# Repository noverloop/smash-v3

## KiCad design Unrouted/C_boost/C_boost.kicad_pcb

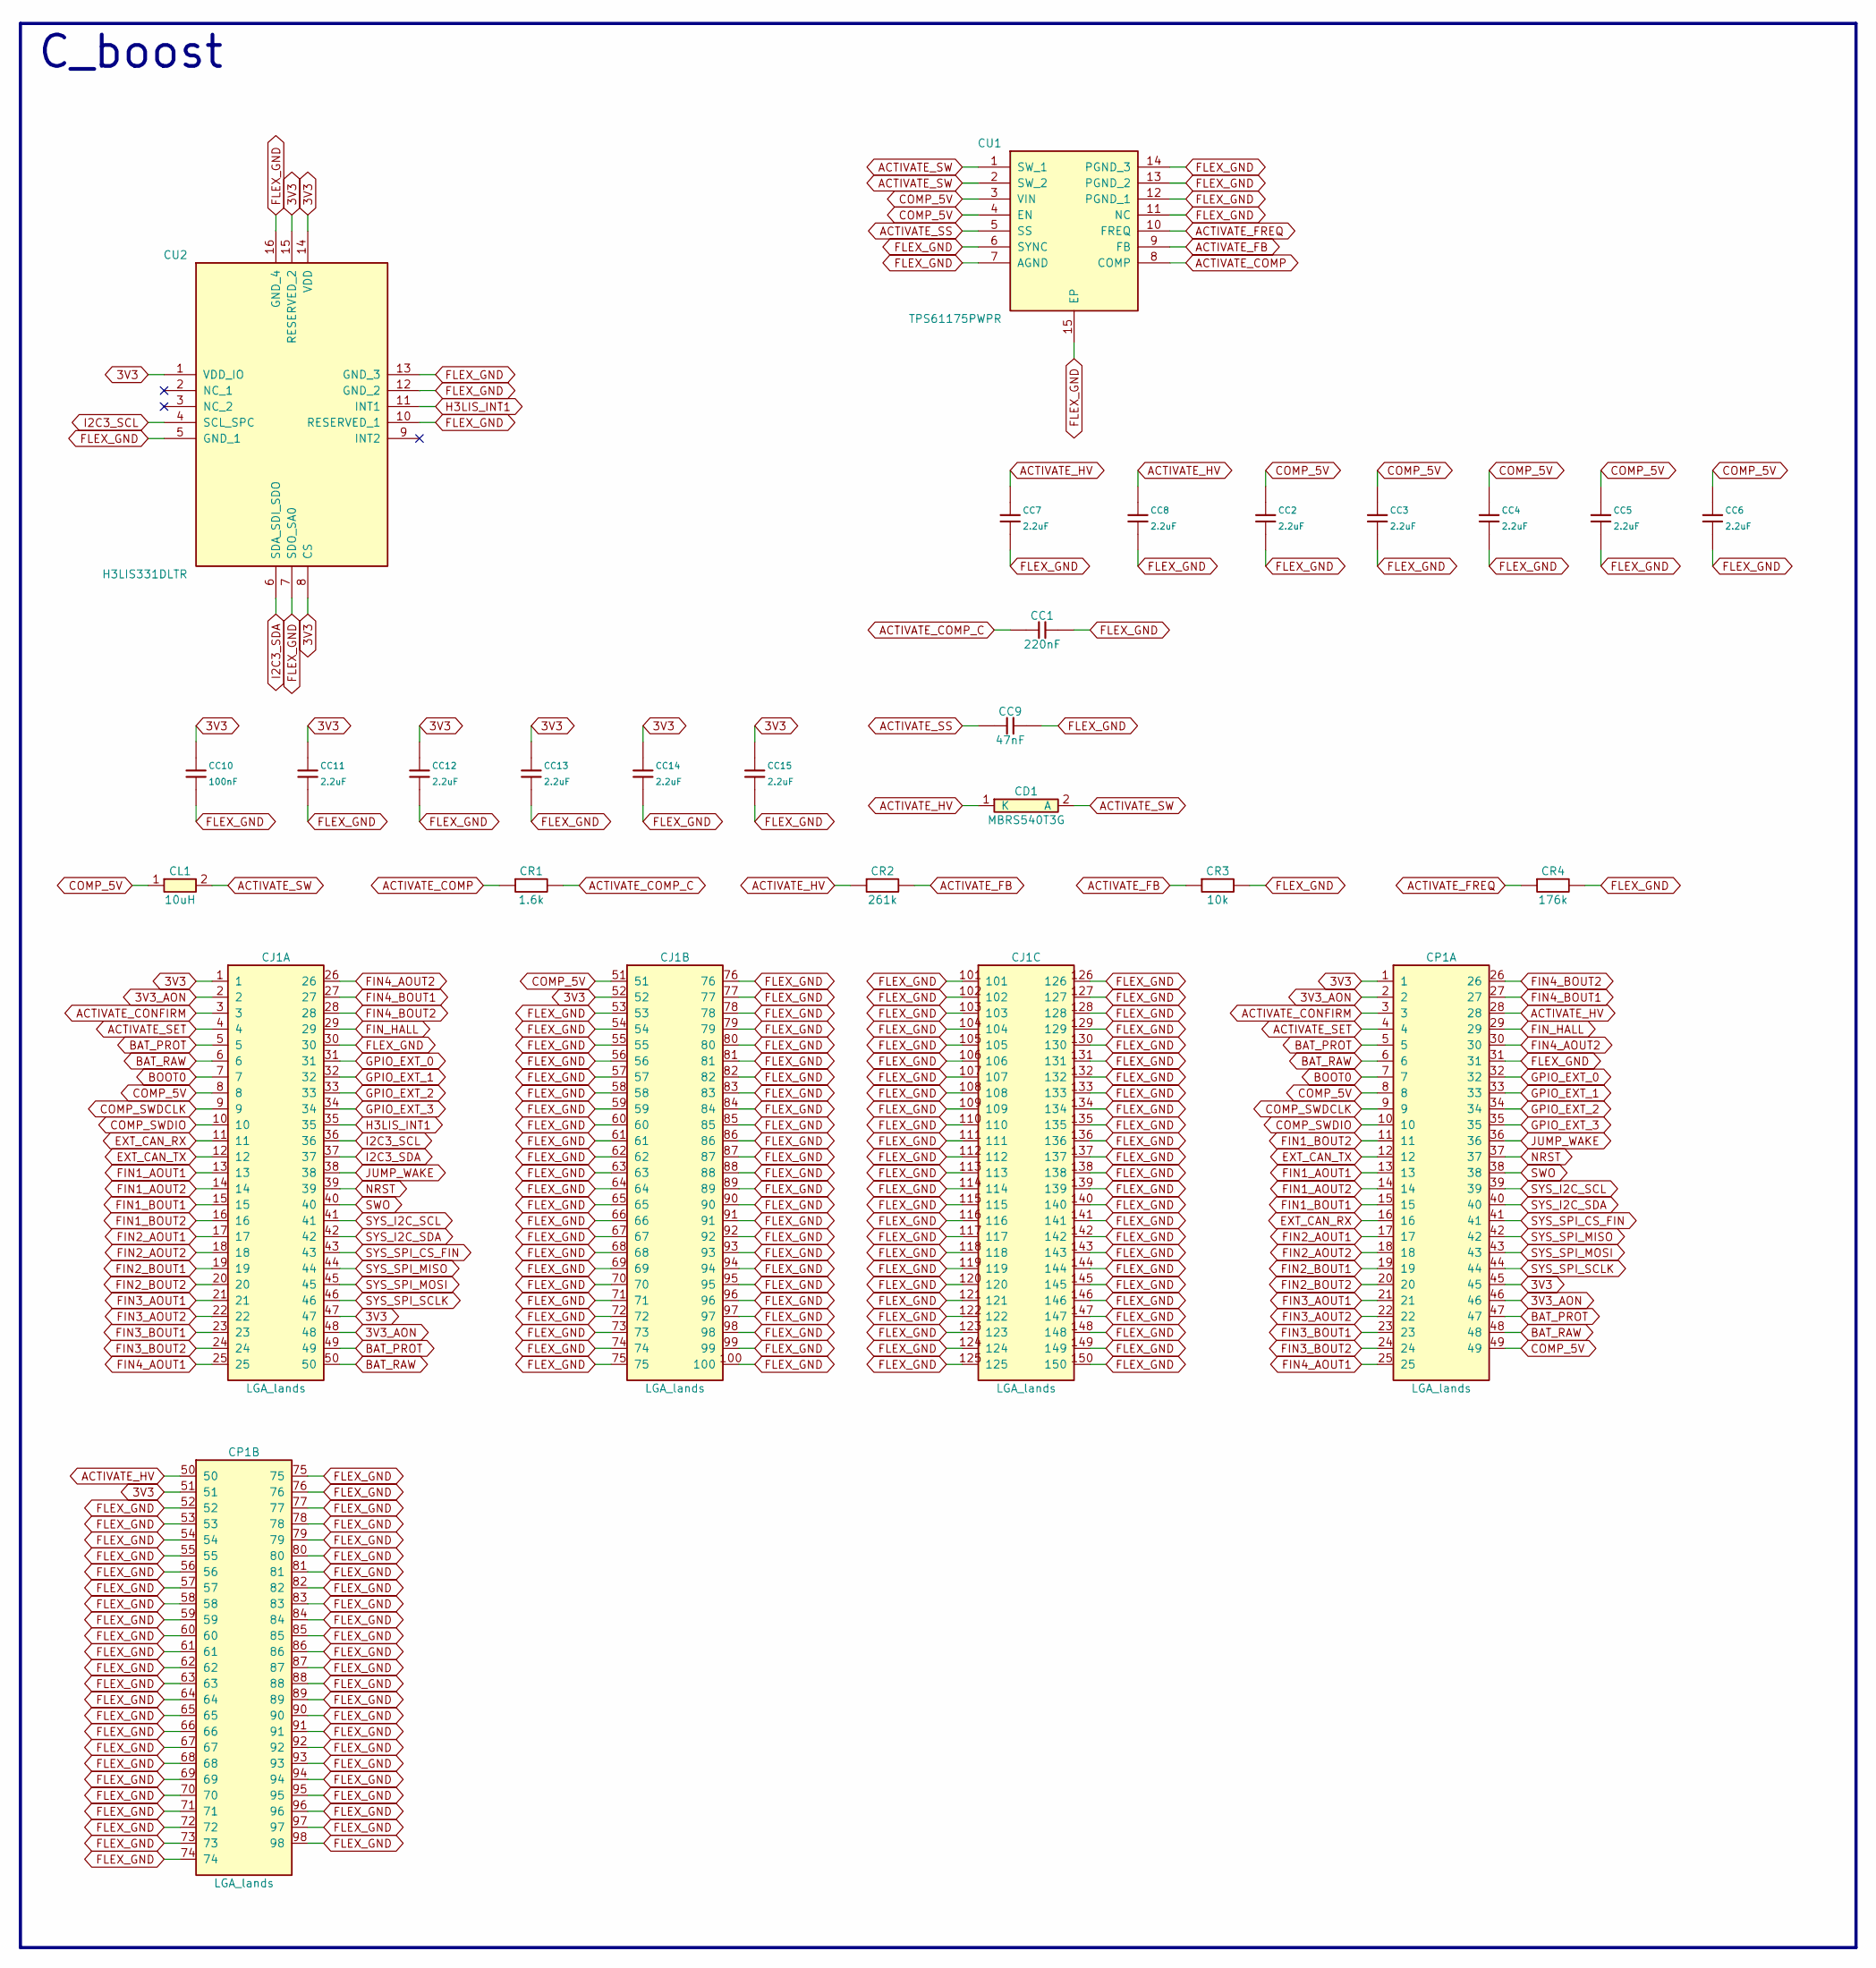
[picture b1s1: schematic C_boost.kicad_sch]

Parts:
CC1: 220nF; Capacitor_SMD_C_0603_1608Metric; MPN C-Series MIL-PRF-32535 X7R 0603 220nF
CC2, CC3, CC4, CC5, CC6, CC7, CC8, CC11, CC12, CC13, CC14, CC15: 2.2uF; Capacitor_SMD_C_0603_1608Metric; MPN C-Series MIL-PRF-32535 X7R 0603 2.2uF
CC9: 47nF; Capacitor_SMD_C_0402_1005Metric; MPN C0402 X7R 47nF
CC10: 100nF; Capacitor_SMD_C_0402_1005Metric; MPN C0402 X7R 100nF
CD1: MBRS540T3G; DIOM7958X256N; MPN MBRS540T3G
CJ1: LGA_lands; J_activation_interface_spacer_activation_interface_cell_flo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; MPN LGA_lands
CL1: 10uH; INDPM4848X280N; MPN 744043100
CP1: LGA_lands; P_activation_interface_spacer_aft_end_board_activation_inte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; MPN LGA_lands
CR1: 1.6k; Resistor_SMD_R_0402_1005Metric; MPN CRCW0402 1.6k 1% e3
CR2: 261k; Resistor_SMD_R_0402_1005Metric; MPN CRCW0402 261k 1% e3
CR3: 10k; Resistor_SMD_R_0402_1005Metric; MPN CRCW0402 10k 1% e3
CR4: 176k; Resistor_SMD_R_0402_1005Metric; MPN CRCW0402 176k 1% e3
CU1: TPS61175PWPR; SOP65P640X120-15N; MPN TPS61175PWPR
CU2: H3LIS331DLTR; LIS3DHTR (LGA-16); MPN H3LIS331DLTR

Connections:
3V3: CC10.1, CC11.1, CC12.1, CC13.1, CC14.1, CC15.1, CJ1.1, CJ1.47, CJ1.52, CP1.1, CP1.45, CP1.51, CU2.1 (VDD_IO), CU2.8 (CS), CU2.14 (VDD), CU2.15 (RESERVED_2)
3V3_AON: CJ1.2, CJ1.48, CP1.2, CP1.46
ACTIVATE_COMP: CR1.1, CU1.8 (COMP)
ACTIVATE_COMP_C: CC1.1, CR1.2
ACTIVATE_CONFIRM: CJ1.3, CP1.3
ACTIVATE_FB: CR2.2, CR3.1, CU1.9 (FB)
ACTIVATE_FREQ: CR4.1, CU1.10 (FREQ)
ACTIVATE_HV: CC7.1, CC8.1, CD1.1 (K), CP1.28, CP1.50, CR2.1
ACTIVATE_SET: CJ1.4, CP1.4
ACTIVATE_SS: CC9.1, CU1.5 (SS)
ACTIVATE_SW: CD1.2 (A), CL1.2, CU1.1 (SW_1), CU1.2 (SW_2)
BAT_PROT: CJ1.5, CJ1.49, CP1.5, CP1.47
BAT_RAW: CJ1.6, CJ1.50, CP1.6, CP1.48
BOOT0: CJ1.7, CP1.7
COMP_5V: CC2.1, CC3.1, CC4.1, CC5.1, CC6.1, CJ1.8, CJ1.51, CL1.1, CP1.8, CP1.49, CU1.3 (VIN), CU1.4 (EN)
COMP_SWDCLK: CJ1.9, CP1.9
COMP_SWDIO: CJ1.10, CP1.10
EXT_CAN_RX: CJ1.11, CP1.16
EXT_CAN_TX: CJ1.12, CP1.12
FIN1_AOUT1: CJ1.13, CP1.13
FIN1_AOUT2: CJ1.14, CP1.14
FIN1_BOUT1: CJ1.15, CP1.15
FIN1_BOUT2: CJ1.16, CP1.11
FIN2_AOUT1: CJ1.17, CP1.17
FIN2_AOUT2: CJ1.18, CP1.18
FIN2_BOUT1: CJ1.19, CP1.19
FIN2_BOUT2: CJ1.20, CP1.20
FIN3_AOUT1: CJ1.21, CP1.21
FIN3_AOUT2: CJ1.22, CP1.22
FIN3_BOUT1: CJ1.23, CP1.23
FIN3_BOUT2: CJ1.24, CP1.24
FIN4_AOUT1: CJ1.25, CP1.25
FIN4_AOUT2: CJ1.26, CP1.30
FIN4_BOUT1: CJ1.27, CP1.27
FIN4_BOUT2: CJ1.28, CP1.26
FIN_HALL: CJ1.29, CP1.29
FLEX_GND: CC1.2, CC2.2, CC3.2, CC4.2, CC5.2, CC6.2, CC7.2, CC8.2, CC9.2, CC10.2, CC11.2, CC12.2, CC13.2, CC14.2, CC15.2, CJ1.30, CJ1.53, CJ1.54, CJ1.55, CJ1.56, CJ1.57, CJ1.58, CJ1.59, CJ1.60, CJ1.61, CJ1.62, CJ1.63, CJ1.64, CJ1.65, CJ1.66, CJ1.67, CJ1.68, CJ1.69, CJ1.70, CJ1.71, CJ1.72, CJ1.73, CJ1.74, CJ1.75, CJ1.76, CJ1.77, CJ1.78, CJ1.79, CJ1.80, CJ1.81, CJ1.82, CJ1.83, CJ1.84, CJ1.85, CJ1.86, CJ1.87, CJ1.88, CJ1.89, CJ1.90, CJ1.91, CJ1.92, CJ1.93, CJ1.94, CJ1.95, CJ1.96, CJ1.97, CJ1.98, CJ1.99, CJ1.100, CJ1.101, CJ1.102, CJ1.103, CJ1.104, CJ1.105, CJ1.106, CJ1.107, CJ1.108, CJ1.109, CJ1.110, CJ1.111, CJ1.112, CJ1.113, CJ1.114, CJ1.115, CJ1.116, CJ1.117, CJ1.118, CJ1.119, CJ1.120, CJ1.121, CJ1.122, CJ1.123, CJ1.124, CJ1.125, CJ1.126, CJ1.127, CJ1.128, CJ1.129, CJ1.130, CJ1.131, CJ1.132, CJ1.133, CJ1.134, CJ1.135, CJ1.136, CJ1.137, CJ1.138, CJ1.139, CJ1.140, CJ1.141, CJ1.142, CJ1.143, CJ1.144, CJ1.145, CJ1.146, CJ1.147, CJ1.148, CJ1.149, CJ1.150, CP1.31, CP1.52, CP1.53, CP1.54, CP1.55, CP1.56, CP1.57, CP1.58, CP1.59, CP1.60, CP1.61, CP1.62, CP1.63, CP1.64, CP1.65, CP1.66, CP1.67, CP1.68, CP1.69, CP1.70, CP1.71, CP1.72, CP1.73, CP1.74, CP1.75, CP1.76, CP1.77, CP1.78, CP1.79, CP1.80, CP1.81, CP1.82, CP1.83, CP1.84, CP1.85, CP1.86, CP1.87, CP1.88, CP1.89, CP1.90, CP1.91, CP1.92, CP1.93, CP1.94, CP1.95, CP1.96, CP1.97, CP1.98, CR3.2, CR4.2, CU1.6 (SYNC), CU1.7 (AGND), CU1.11 (NC), CU1.12 (PGND_1), CU1.13 (PGND_2), CU1.14 (PGND_3), CU1.15 (EP), CU2.5 (GND_1), CU2.7 (SDO_SA0), CU2.10 (RESERVED_1), CU2.12 (GND_2), CU2.13 (GND_3), CU2.16 (GND_4)
GPIO_EXT_0: CJ1.31, CP1.32
GPIO_EXT_1: CJ1.32, CP1.33
GPIO_EXT_2: CJ1.33, CP1.34
GPIO_EXT_3: CJ1.34, CP1.35
H3LIS_INT1: CJ1.35, CU2.11 (INT1)
I2C3_SCL: CJ1.36, CU2.4 (SCL_SPC)
I2C3_SDA: CJ1.37, CU2.6 (SDA_SDI_SDO)
JUMP_WAKE: CJ1.38, CP1.36
NRST: CJ1.39, CP1.37
SWO: CJ1.40, CP1.38
SYS_I2C_SCL: CJ1.41, CP1.39
SYS_I2C_SDA: CJ1.42, CP1.40
SYS_SPI_CS_FIN: CJ1.43, CP1.41
SYS_SPI_MISO: CJ1.44, CP1.42
SYS_SPI_MOSI: CJ1.45, CP1.43
SYS_SPI_SCLK: CJ1.46, CP1.44

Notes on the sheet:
C_boost

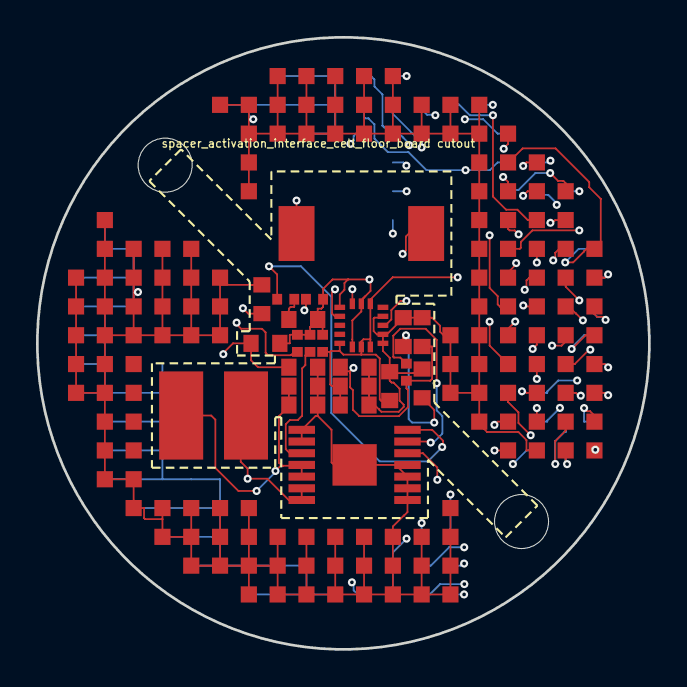
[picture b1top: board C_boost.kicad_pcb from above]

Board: 14 copper layers, 34.0 x 34.0 mm, 27 parts (1 on the bottom side), 53 nets.

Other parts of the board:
CMH1, CMH2: smash_mech_potting

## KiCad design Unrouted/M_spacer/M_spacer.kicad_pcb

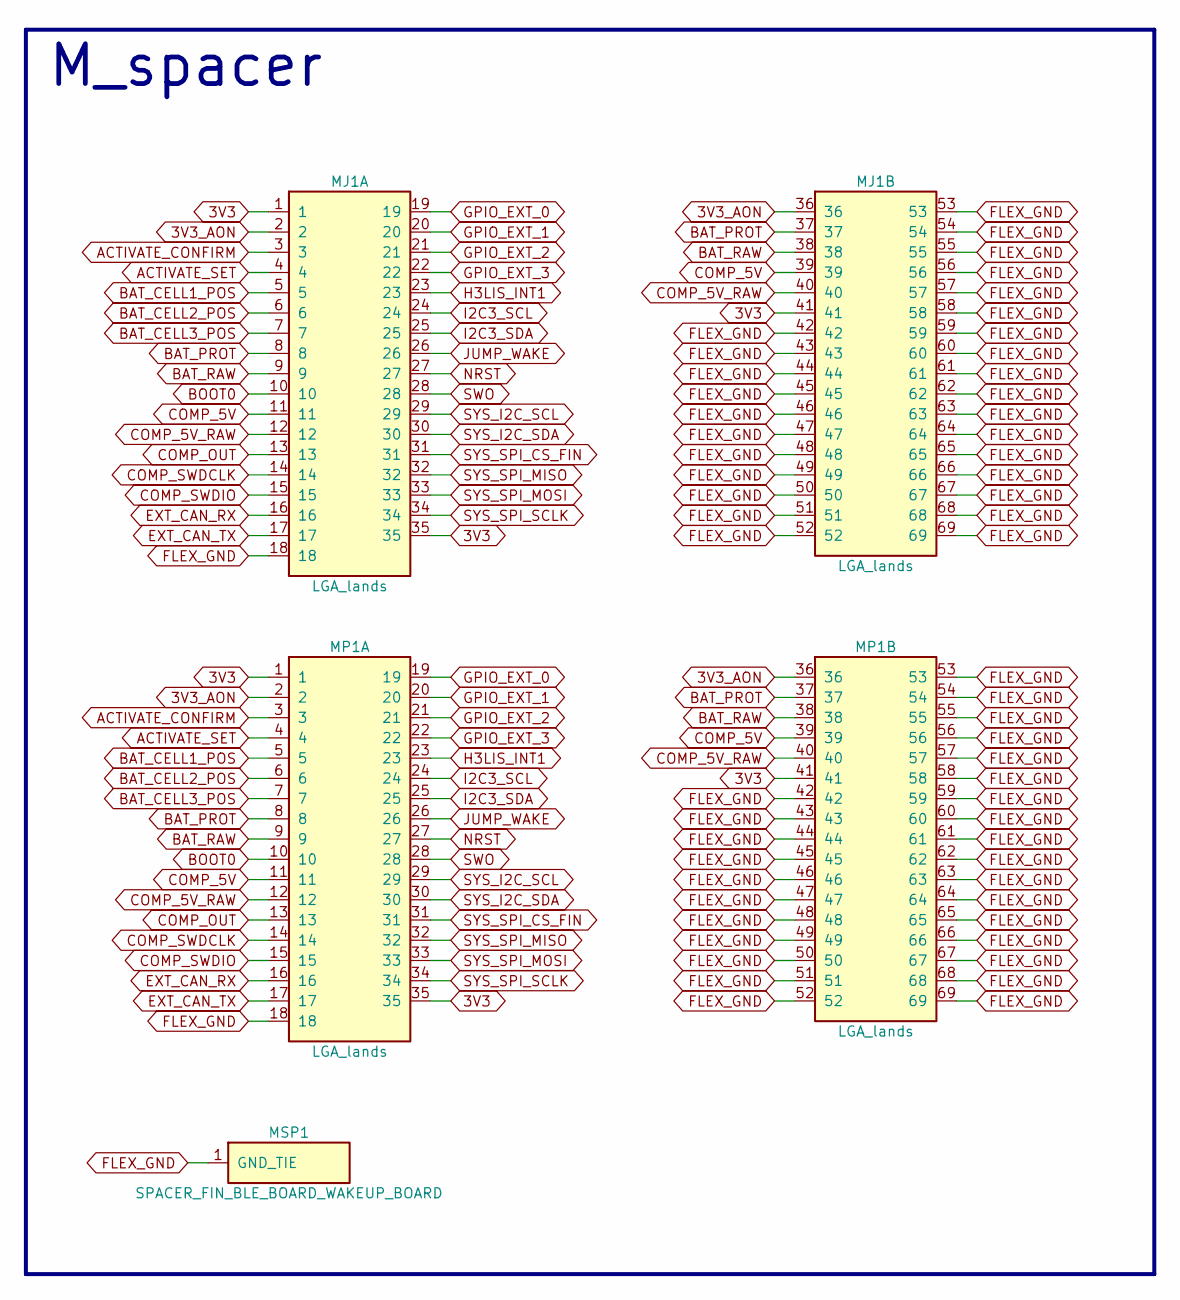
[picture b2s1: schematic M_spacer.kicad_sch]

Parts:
MJ1: LGA_lands; J_spacer_fin_ble_board_wakeup_board_top; MPN LGA_lands
MP1: LGA_lands; P_spacer_fin_ble_board_wakeup_board_bot; MPN LGA_lands
MSP1: SPACER_FIN_BLE_BOARD_WAKEUP_BOARD; Spacer_Mechanical_34mm

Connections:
3V3: MJ1.1, MJ1.35, MJ1.41, MP1.1, MP1.35, MP1.41
3V3_AON: MJ1.2, MJ1.36, MP1.2, MP1.36
ACTIVATE_CONFIRM: MJ1.3, MP1.3
ACTIVATE_SET: MJ1.4, MP1.4
BAT_CELL1_POS: MJ1.5, MP1.5
BAT_CELL2_POS: MJ1.6, MP1.6
BAT_CELL3_POS: MJ1.7, MP1.7
BAT_PROT: MJ1.8, MJ1.37, MP1.8, MP1.37
BAT_RAW: MJ1.9, MJ1.38, MP1.9, MP1.38
BOOT0: MJ1.10, MP1.10
COMP_5V: MJ1.11, MJ1.39, MP1.11, MP1.39
COMP_5V_RAW: MJ1.12, MJ1.40, MP1.12, MP1.40
COMP_OUT: MJ1.13, MP1.13
COMP_SWDCLK: MJ1.14, MP1.14
COMP_SWDIO: MJ1.15, MP1.15
EXT_CAN_RX: MJ1.16, MP1.16
EXT_CAN_TX: MJ1.17, MP1.17
FLEX_GND: MJ1.18, MJ1.42, MJ1.43, MJ1.44, MJ1.45, MJ1.46, MJ1.47, MJ1.48, MJ1.49, MJ1.50, MJ1.51, MJ1.52, MJ1.53, MJ1.54, MJ1.55, MJ1.56, MJ1.57, MJ1.58, MJ1.59, MJ1.60, MJ1.61, MJ1.62, MJ1.63, MJ1.64, MJ1.65, MJ1.66, MJ1.67, MJ1.68, MJ1.69, MP1.18, MP1.42, MP1.43, MP1.44, MP1.45, MP1.46, MP1.47, MP1.48, MP1.49, MP1.50, MP1.51, MP1.52, MP1.53, MP1.54, MP1.55, MP1.56, MP1.57, MP1.58, MP1.59, MP1.60, MP1.61, MP1.62, MP1.63, MP1.64, MP1.65, MP1.66, MP1.67, MP1.68, MP1.69, MSP1.1
GPIO_EXT_0: MJ1.19, MP1.19
GPIO_EXT_1: MJ1.20, MP1.20
GPIO_EXT_2: MJ1.21, MP1.21
GPIO_EXT_3: MJ1.22, MP1.22
H3LIS_INT1: MJ1.23, MP1.23
I2C3_SCL: MJ1.24, MP1.24
I2C3_SDA: MJ1.25, MP1.25
JUMP_WAKE: MJ1.26, MP1.26
NRST: MJ1.27, MP1.27
SWO: MJ1.28, MP1.28
SYS_I2C_SCL: MJ1.29, MP1.29
SYS_I2C_SDA: MJ1.30, MP1.30
SYS_SPI_CS_FIN: MJ1.31, MP1.31
SYS_SPI_MISO: MJ1.32, MP1.32
SYS_SPI_MOSI: MJ1.33, MP1.33
SYS_SPI_SCLK: MJ1.34, MP1.34

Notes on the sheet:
M_spacer

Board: 2 copper layers, 5 parts (1 on the bottom side), 34 nets, no tracks yet.

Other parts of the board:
MMH1, MMH2: smash_mech_potting

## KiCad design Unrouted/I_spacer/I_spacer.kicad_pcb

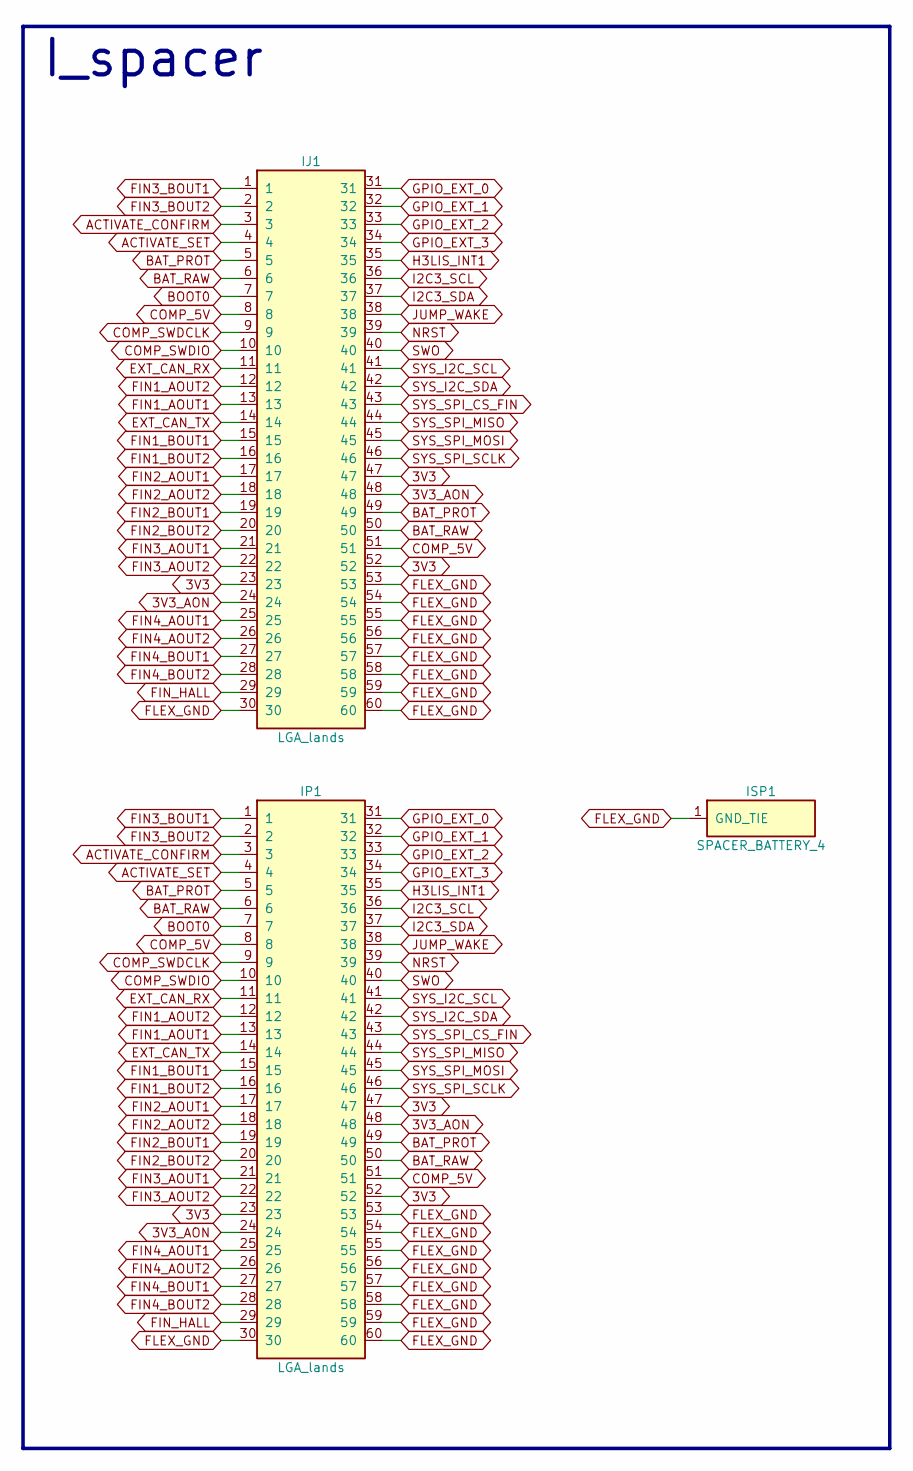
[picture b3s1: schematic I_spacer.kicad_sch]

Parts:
IJ1: LGA_lands; J_spacer_battery_4_top; MPN LGA_lands
IP1: LGA_lands; P_spacer_battery_4_bot; MPN LGA_lands
ISP1: SPACER_BATTERY_4; Spacer_Mechanical_34mm

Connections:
3V3: IJ1.23, IJ1.47, IJ1.52, IP1.23, IP1.47, IP1.52
3V3_AON: IJ1.24, IJ1.48, IP1.24, IP1.48
ACTIVATE_CONFIRM: IJ1.3, IP1.3
ACTIVATE_SET: IJ1.4, IP1.4
BAT_PROT: IJ1.5, IJ1.49, IP1.5, IP1.49
BAT_RAW: IJ1.6, IJ1.50, IP1.6, IP1.50
BOOT0: IJ1.7, IP1.7
COMP_5V: IJ1.8, IJ1.51, IP1.8, IP1.51
COMP_SWDCLK: IJ1.9, IP1.9
COMP_SWDIO: IJ1.10, IP1.10
EXT_CAN_RX: IJ1.11, IP1.11
EXT_CAN_TX: IJ1.14, IP1.14
FIN1_AOUT1: IJ1.13, IP1.13
FIN1_AOUT2: IJ1.12, IP1.12
FIN1_BOUT1: IJ1.15, IP1.15
FIN1_BOUT2: IJ1.16, IP1.16
FIN2_AOUT1: IJ1.17, IP1.17
FIN2_AOUT2: IJ1.18, IP1.18
FIN2_BOUT1: IJ1.19, IP1.19
FIN2_BOUT2: IJ1.20, IP1.20
FIN3_AOUT1: IJ1.21, IP1.21
FIN3_AOUT2: IJ1.22, IP1.22
FIN3_BOUT1: IJ1.1, IP1.1
FIN3_BOUT2: IJ1.2, IP1.2
FIN4_AOUT1: IJ1.25, IP1.25
FIN4_AOUT2: IJ1.26, IP1.26
FIN4_BOUT1: IJ1.27, IP1.27
FIN4_BOUT2: IJ1.28, IP1.28
FIN_HALL: IJ1.29, IP1.29
FLEX_GND: IJ1.30, IJ1.53, IJ1.54, IJ1.55, IJ1.56, IJ1.57, IJ1.58, IJ1.59, IJ1.60, IP1.30, IP1.53, IP1.54, IP1.55, IP1.56, IP1.57, IP1.58, IP1.59, IP1.60, ISP1.1
GPIO_EXT_0: IJ1.31, IP1.31
GPIO_EXT_1: IJ1.32, IP1.32
GPIO_EXT_2: IJ1.33, IP1.33
GPIO_EXT_3: IJ1.34, IP1.34
H3LIS_INT1: IJ1.35, IP1.35
I2C3_SCL: IJ1.36, IP1.36
I2C3_SDA: IJ1.37, IP1.37
JUMP_WAKE: IJ1.38, IP1.38
NRST: IJ1.39, IP1.39
SWO: IJ1.40, IP1.40
SYS_I2C_SCL: IJ1.41, IP1.41
SYS_I2C_SDA: IJ1.42, IP1.42
SYS_SPI_CS_FIN: IJ1.43, IP1.43
SYS_SPI_MISO: IJ1.44, IP1.44
SYS_SPI_MOSI: IJ1.45, IP1.45
SYS_SPI_SCLK: IJ1.46, IP1.46

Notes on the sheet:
I_spacer

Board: 2 copper layers, 4 parts (1 on the bottom side), 46 nets, no tracks yet.

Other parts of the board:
IMH1: smash_mech_potting

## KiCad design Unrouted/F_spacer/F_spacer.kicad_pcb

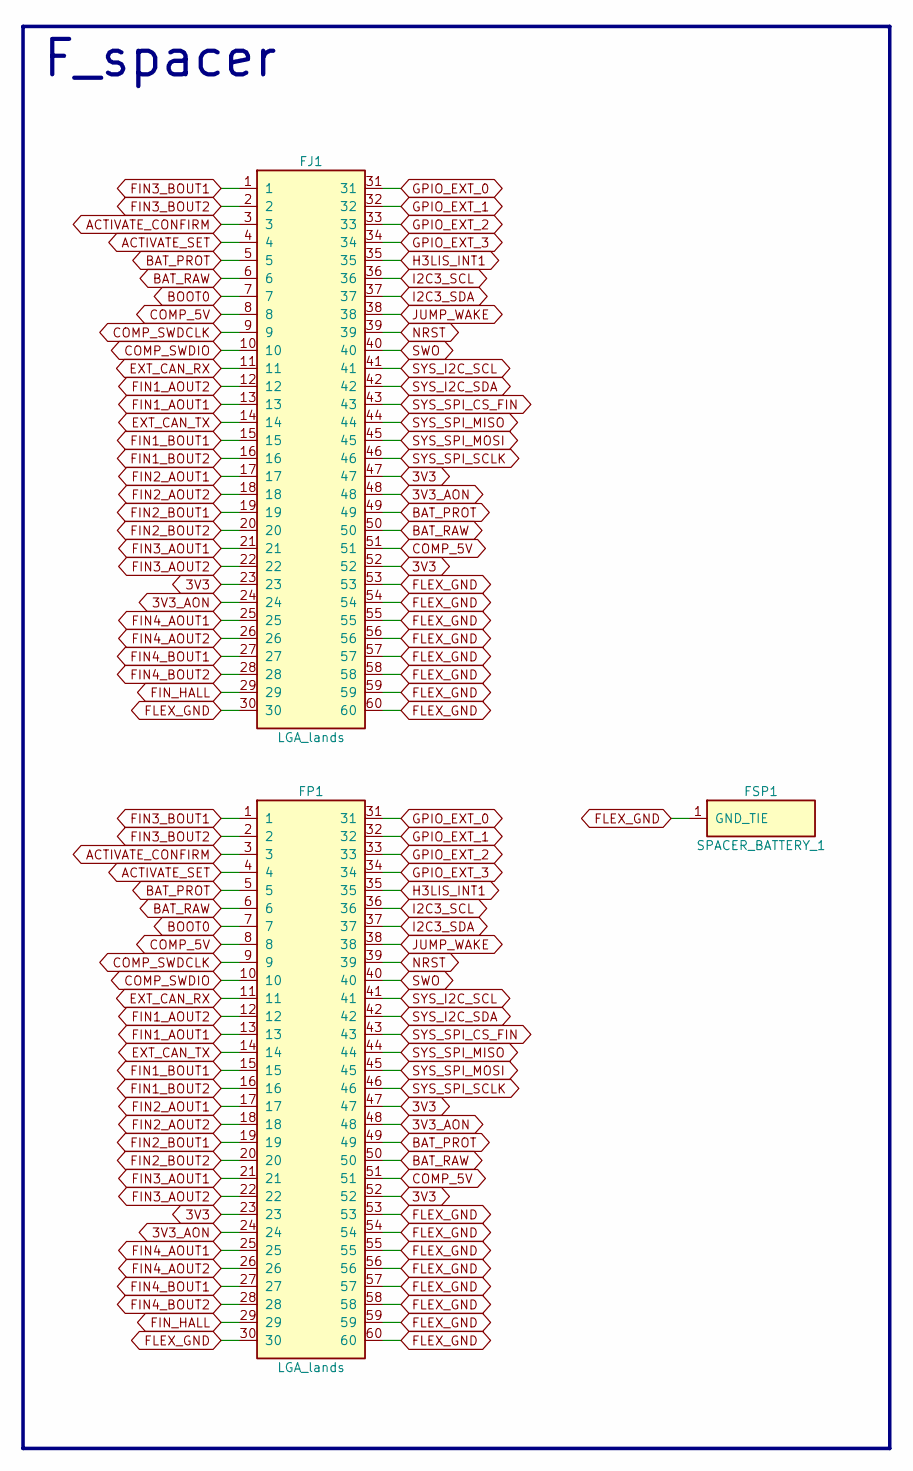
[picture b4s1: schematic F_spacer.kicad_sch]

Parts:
FJ1: LGA_lands; J_spacer_battery_1_top; MPN LGA_lands
FP1: LGA_lands; P_spacer_battery_1_bot; MPN LGA_lands
FSP1: SPACER_BATTERY_1; Spacer_Mechanical_34mm

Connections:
3V3: FJ1.23, FJ1.47, FJ1.52, FP1.23, FP1.47, FP1.52
3V3_AON: FJ1.24, FJ1.48, FP1.24, FP1.48
ACTIVATE_CONFIRM: FJ1.3, FP1.3
ACTIVATE_SET: FJ1.4, FP1.4
BAT_PROT: FJ1.5, FJ1.49, FP1.5, FP1.49
BAT_RAW: FJ1.6, FJ1.50, FP1.6, FP1.50
BOOT0: FJ1.7, FP1.7
COMP_5V: FJ1.8, FJ1.51, FP1.8, FP1.51
COMP_SWDCLK: FJ1.9, FP1.9
COMP_SWDIO: FJ1.10, FP1.10
EXT_CAN_RX: FJ1.11, FP1.11
EXT_CAN_TX: FJ1.14, FP1.14
FIN1_AOUT1: FJ1.13, FP1.13
FIN1_AOUT2: FJ1.12, FP1.12
FIN1_BOUT1: FJ1.15, FP1.15
FIN1_BOUT2: FJ1.16, FP1.16
FIN2_AOUT1: FJ1.17, FP1.17
FIN2_AOUT2: FJ1.18, FP1.18
FIN2_BOUT1: FJ1.19, FP1.19
FIN2_BOUT2: FJ1.20, FP1.20
FIN3_AOUT1: FJ1.21, FP1.21
FIN3_AOUT2: FJ1.22, FP1.22
FIN3_BOUT1: FJ1.1, FP1.1
FIN3_BOUT2: FJ1.2, FP1.2
FIN4_AOUT1: FJ1.25, FP1.25
FIN4_AOUT2: FJ1.26, FP1.26
FIN4_BOUT1: FJ1.27, FP1.27
FIN4_BOUT2: FJ1.28, FP1.28
FIN_HALL: FJ1.29, FP1.29
FLEX_GND: FJ1.30, FJ1.53, FJ1.54, FJ1.55, FJ1.56, FJ1.57, FJ1.58, FJ1.59, FJ1.60, FP1.30, FP1.53, FP1.54, FP1.55, FP1.56, FP1.57, FP1.58, FP1.59, FP1.60, FSP1.1
GPIO_EXT_0: FJ1.31, FP1.31
GPIO_EXT_1: FJ1.32, FP1.32
GPIO_EXT_2: FJ1.33, FP1.33
GPIO_EXT_3: FJ1.34, FP1.34
H3LIS_INT1: FJ1.35, FP1.35
I2C3_SCL: FJ1.36, FP1.36
I2C3_SDA: FJ1.37, FP1.37
JUMP_WAKE: FJ1.38, FP1.38
NRST: FJ1.39, FP1.39
SWO: FJ1.40, FP1.40
SYS_I2C_SCL: FJ1.41, FP1.41
SYS_I2C_SDA: FJ1.42, FP1.42
SYS_SPI_CS_FIN: FJ1.43, FP1.43
SYS_SPI_MISO: FJ1.44, FP1.44
SYS_SPI_MOSI: FJ1.45, FP1.45
SYS_SPI_SCLK: FJ1.46, FP1.46

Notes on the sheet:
F_spacer

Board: 2 copper layers, 4 parts (1 on the bottom side), 46 nets, no tracks yet.

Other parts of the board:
FMH1: smash_mech_potting

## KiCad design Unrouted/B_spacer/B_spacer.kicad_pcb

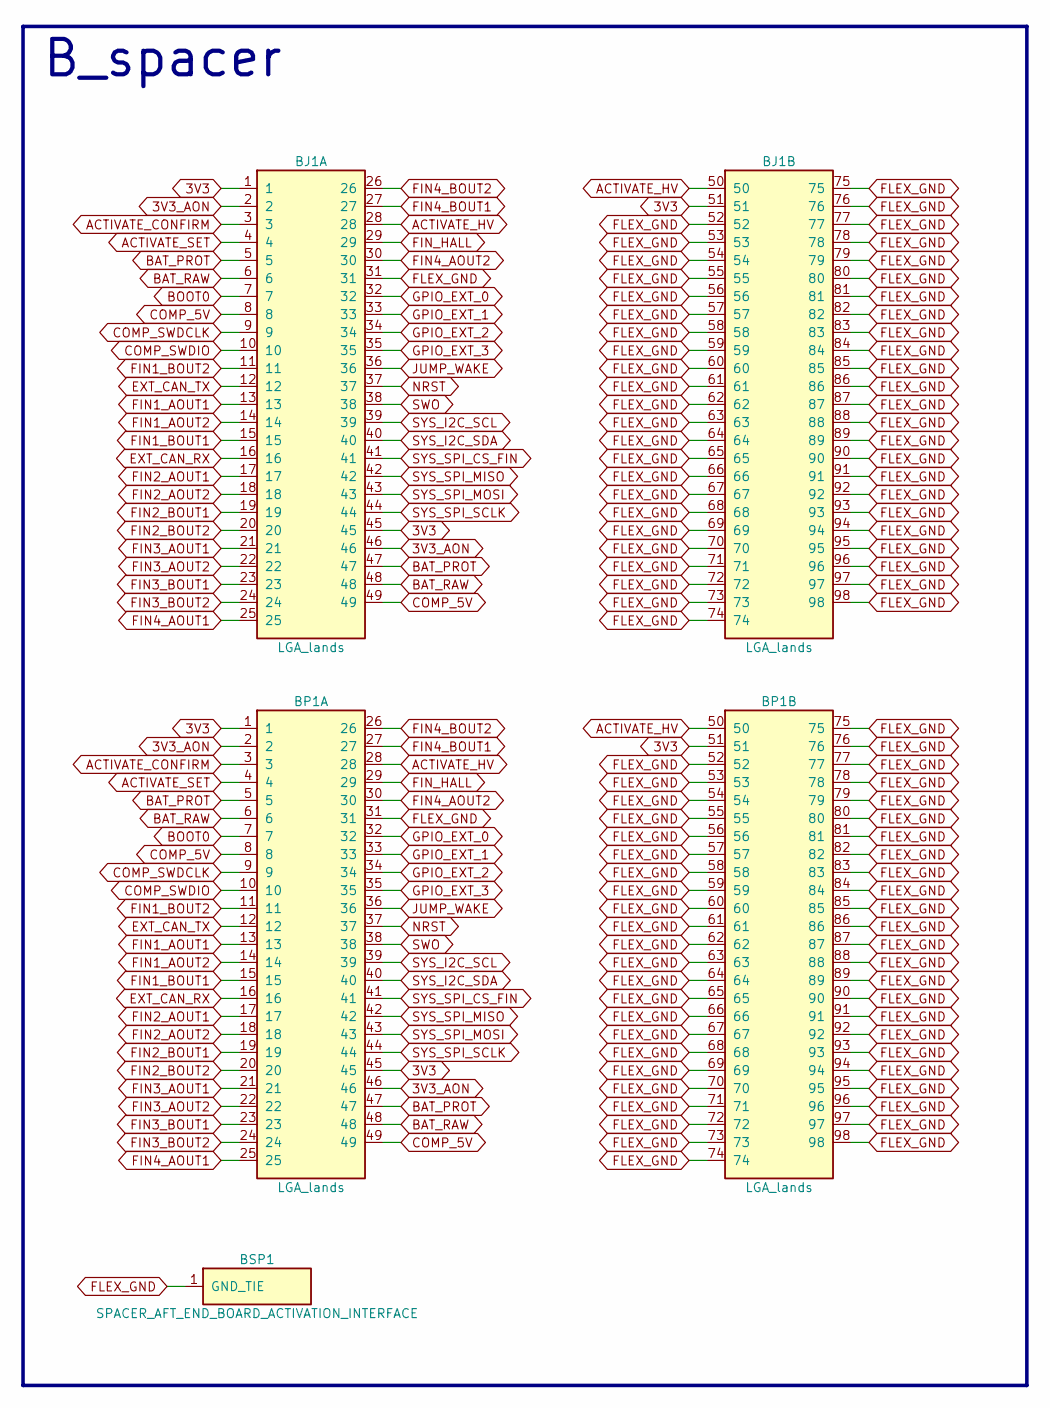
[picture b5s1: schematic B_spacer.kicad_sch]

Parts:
BJ1: LGA_lands; J_spacer_aft_end_board_activation_interface_top; MPN LGA_lands
BP1: LGA_lands; P_spacer_aft_end_board_activation_interface_bot; MPN LGA_lands
BSP1: SPACER_AFT_END_BOARD_ACTIVATION_INTERFACE; Spacer_Mechanical_34mm

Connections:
3V3: BJ1.1, BJ1.45, BJ1.51, BP1.1, BP1.45, BP1.51
3V3_AON: BJ1.2, BJ1.46, BP1.2, BP1.46
ACTIVATE_CONFIRM: BJ1.3, BP1.3
ACTIVATE_HV: BJ1.28, BJ1.50, BP1.28, BP1.50
ACTIVATE_SET: BJ1.4, BP1.4
BAT_PROT: BJ1.5, BJ1.47, BP1.5, BP1.47
BAT_RAW: BJ1.6, BJ1.48, BP1.6, BP1.48
BOOT0: BJ1.7, BP1.7
COMP_5V: BJ1.8, BJ1.49, BP1.8, BP1.49
COMP_SWDCLK: BJ1.9, BP1.9
COMP_SWDIO: BJ1.10, BP1.10
EXT_CAN_RX: BJ1.16, BP1.16
EXT_CAN_TX: BJ1.12, BP1.12
FIN1_AOUT1: BJ1.13, BP1.13
FIN1_AOUT2: BJ1.14, BP1.14
FIN1_BOUT1: BJ1.15, BP1.15
FIN1_BOUT2: BJ1.11, BP1.11
FIN2_AOUT1: BJ1.17, BP1.17
FIN2_AOUT2: BJ1.18, BP1.18
FIN2_BOUT1: BJ1.19, BP1.19
FIN2_BOUT2: BJ1.20, BP1.20
FIN3_AOUT1: BJ1.21, BP1.21
FIN3_AOUT2: BJ1.22, BP1.22
FIN3_BOUT1: BJ1.23, BP1.23
FIN3_BOUT2: BJ1.24, BP1.24
FIN4_AOUT1: BJ1.25, BP1.25
FIN4_AOUT2: BJ1.30, BP1.30
FIN4_BOUT1: BJ1.27, BP1.27
FIN4_BOUT2: BJ1.26, BP1.26
FIN_HALL: BJ1.29, BP1.29
FLEX_GND: BJ1.31, BJ1.52, BJ1.53, BJ1.54, BJ1.55, BJ1.56, BJ1.57, BJ1.58, BJ1.59, BJ1.60, BJ1.61, BJ1.62, BJ1.63, BJ1.64, BJ1.65, BJ1.66, BJ1.67, BJ1.68, BJ1.69, BJ1.70, BJ1.71, BJ1.72, BJ1.73, BJ1.74, BJ1.75, BJ1.76, BJ1.77, BJ1.78, BJ1.79, BJ1.80, BJ1.81, BJ1.82, BJ1.83, BJ1.84, BJ1.85, BJ1.86, BJ1.87, BJ1.88, BJ1.89, BJ1.90, BJ1.91, BJ1.92, BJ1.93, BJ1.94, BJ1.95, BJ1.96, BJ1.97, BJ1.98, BP1.31, BP1.52, BP1.53, BP1.54, BP1.55, BP1.56, BP1.57, BP1.58, BP1.59, BP1.60, BP1.61, BP1.62, BP1.63, BP1.64, BP1.65, BP1.66, BP1.67, BP1.68, BP1.69, BP1.70, BP1.71, BP1.72, BP1.73, BP1.74, BP1.75, BP1.76, BP1.77, BP1.78, BP1.79, BP1.80, BP1.81, BP1.82, BP1.83, BP1.84, BP1.85, BP1.86, BP1.87, BP1.88, BP1.89, BP1.90, BP1.91, BP1.92, BP1.93, BP1.94, BP1.95, BP1.96, BP1.97, BP1.98, BSP1.1
GPIO_EXT_0: BJ1.32, BP1.32
GPIO_EXT_1: BJ1.33, BP1.33
GPIO_EXT_2: BJ1.34, BP1.34
GPIO_EXT_3: BJ1.35, BP1.35
JUMP_WAKE: BJ1.36, BP1.36
NRST: BJ1.37, BP1.37
SWO: BJ1.38, BP1.38
SYS_I2C_SCL: BJ1.39, BP1.39
SYS_I2C_SDA: BJ1.40, BP1.40
SYS_SPI_CS_FIN: BJ1.41, BP1.41
SYS_SPI_MISO: BJ1.42, BP1.42
SYS_SPI_MOSI: BJ1.43, BP1.43
SYS_SPI_SCLK: BJ1.44, BP1.44

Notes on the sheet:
B_spacer

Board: 2 copper layers, 5 parts (1 on the bottom side), 44 nets, no tracks yet.

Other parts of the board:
BMH1, BMH2: smash_mech_potting

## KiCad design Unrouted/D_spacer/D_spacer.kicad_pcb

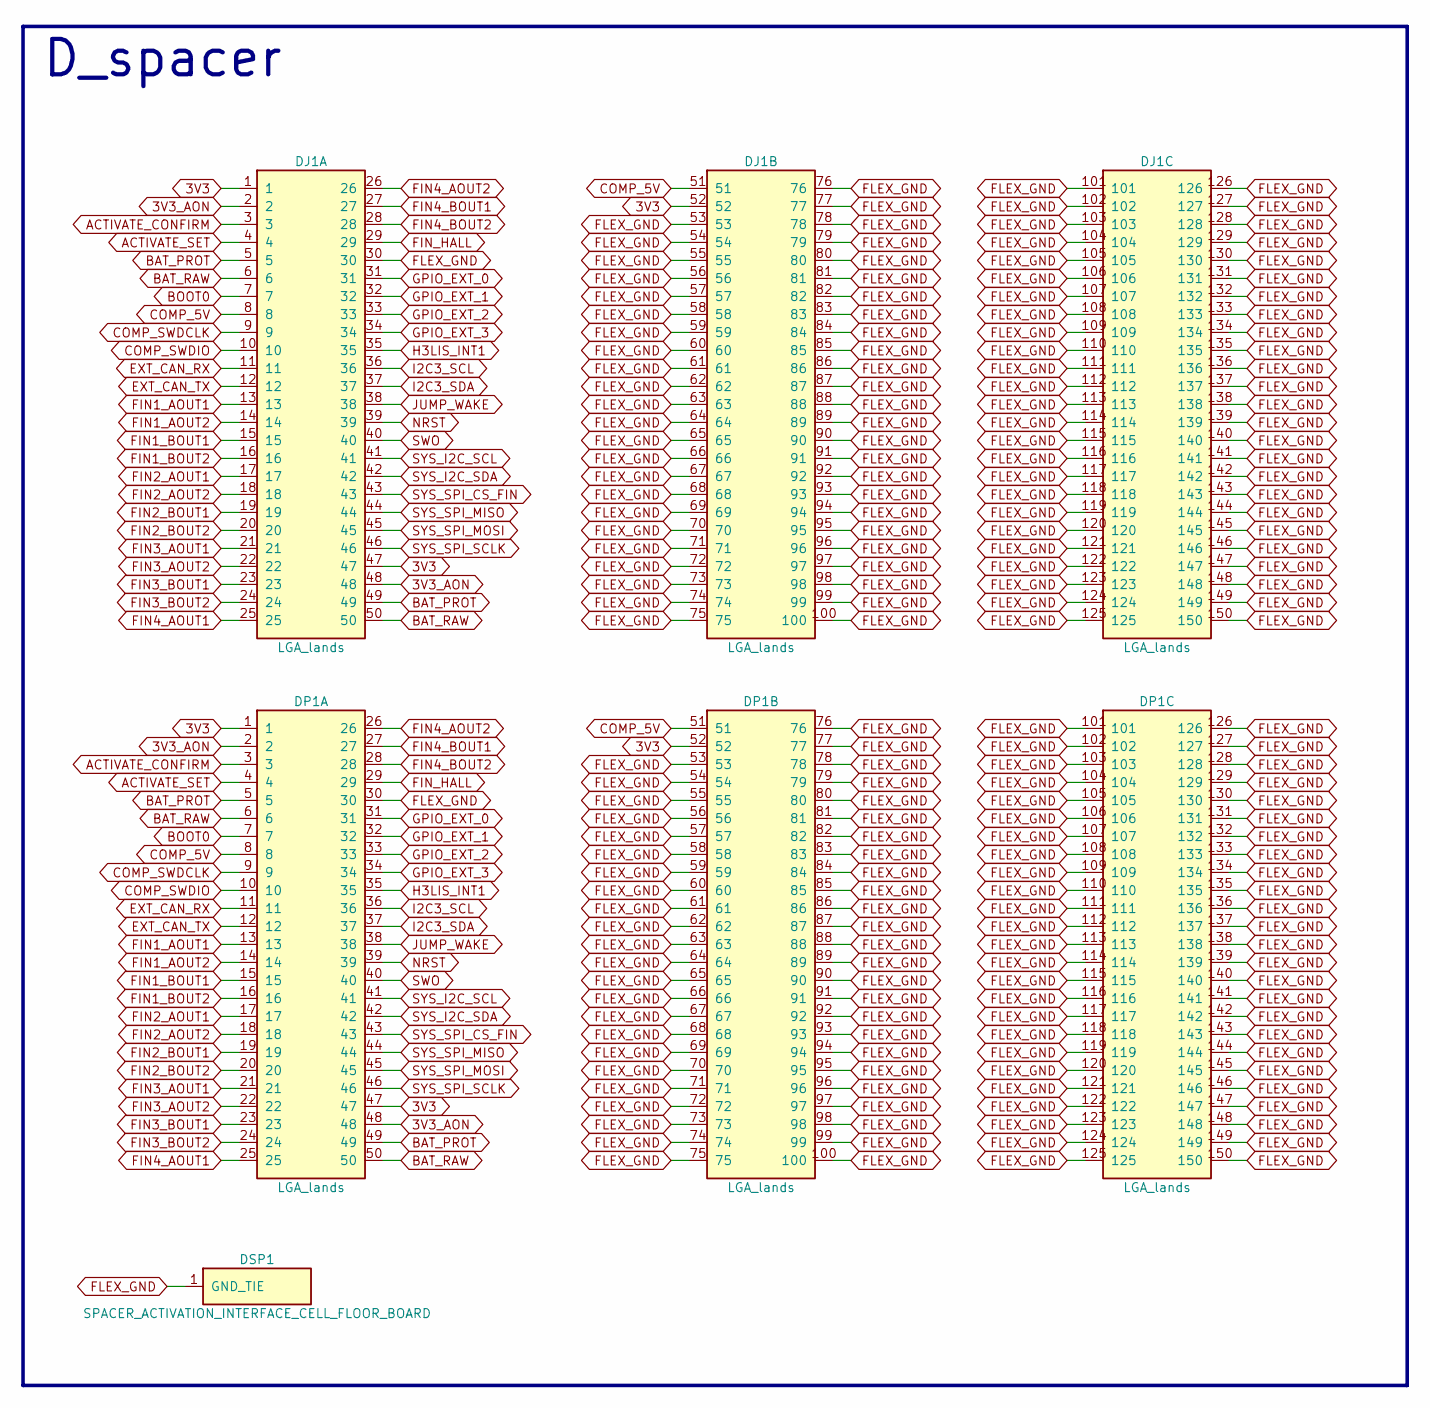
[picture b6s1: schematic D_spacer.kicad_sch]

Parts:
DJ1: LGA_lands; J_spacer_activation_interface_cell_floor_board_top; MPN LGA_lands
DP1: LGA_lands; P_spacer_activation_interface_cell_floor_board_bot; MPN LGA_lands
DSP1: SPACER_ACTIVATION_INTERFACE_CELL_FLOOR_BOARD; Spacer_Mechanical_34mm

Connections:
3V3: DJ1.1, DJ1.47, DJ1.52, DP1.1, DP1.47, DP1.52
3V3_AON: DJ1.2, DJ1.48, DP1.2, DP1.48
ACTIVATE_CONFIRM: DJ1.3, DP1.3
ACTIVATE_SET: DJ1.4, DP1.4
BAT_PROT: DJ1.5, DJ1.49, DP1.5, DP1.49
BAT_RAW: DJ1.6, DJ1.50, DP1.6, DP1.50
BOOT0: DJ1.7, DP1.7
COMP_5V: DJ1.8, DJ1.51, DP1.8, DP1.51
COMP_SWDCLK: DJ1.9, DP1.9
COMP_SWDIO: DJ1.10, DP1.10
EXT_CAN_RX: DJ1.11, DP1.11
EXT_CAN_TX: DJ1.12, DP1.12
FIN1_AOUT1: DJ1.13, DP1.13
FIN1_AOUT2: DJ1.14, DP1.14
FIN1_BOUT1: DJ1.15, DP1.15
FIN1_BOUT2: DJ1.16, DP1.16
FIN2_AOUT1: DJ1.17, DP1.17
FIN2_AOUT2: DJ1.18, DP1.18
FIN2_BOUT1: DJ1.19, DP1.19
FIN2_BOUT2: DJ1.20, DP1.20
FIN3_AOUT1: DJ1.21, DP1.21
FIN3_AOUT2: DJ1.22, DP1.22
FIN3_BOUT1: DJ1.23, DP1.23
FIN3_BOUT2: DJ1.24, DP1.24
FIN4_AOUT1: DJ1.25, DP1.25
FIN4_AOUT2: DJ1.26, DP1.26
FIN4_BOUT1: DJ1.27, DP1.27
FIN4_BOUT2: DJ1.28, DP1.28
FIN_HALL: DJ1.29, DP1.29
FLEX_GND: DJ1.30, DJ1.53, DJ1.54, DJ1.55, DJ1.56, DJ1.57, DJ1.58, DJ1.59, DJ1.60, DJ1.61, DJ1.62, DJ1.63, DJ1.64, DJ1.65, DJ1.66, DJ1.67, DJ1.68, DJ1.69, DJ1.70, DJ1.71, DJ1.72, DJ1.73, DJ1.74, DJ1.75, DJ1.76, DJ1.77, DJ1.78, DJ1.79, DJ1.80, DJ1.81, DJ1.82, DJ1.83, DJ1.84, DJ1.85, DJ1.86, DJ1.87, DJ1.88, DJ1.89, DJ1.90, DJ1.91, DJ1.92, DJ1.93, DJ1.94, DJ1.95, DJ1.96, DJ1.97, DJ1.98, DJ1.99, DJ1.100, DJ1.101, DJ1.102, DJ1.103, DJ1.104, DJ1.105, DJ1.106, DJ1.107, DJ1.108, DJ1.109, DJ1.110, DJ1.111, DJ1.112, DJ1.113, DJ1.114, DJ1.115, DJ1.116, DJ1.117, DJ1.118, DJ1.119, DJ1.120, DJ1.121, DJ1.122, DJ1.123, DJ1.124, DJ1.125, DJ1.126, DJ1.127, DJ1.128, DJ1.129, DJ1.130, DJ1.131, DJ1.132, DJ1.133, DJ1.134, DJ1.135, DJ1.136, DJ1.137, DJ1.138, DJ1.139, DJ1.140, DJ1.141, DJ1.142, DJ1.143, DJ1.144, DJ1.145, DJ1.146, DJ1.147, DJ1.148, DJ1.149, DJ1.150, DP1.30, DP1.53, DP1.54, DP1.55, DP1.56, DP1.57, DP1.58, DP1.59, DP1.60, DP1.61, DP1.62, DP1.63, DP1.64, DP1.65, DP1.66, DP1.67, DP1.68, DP1.69, DP1.70, DP1.71, DP1.72, DP1.73, DP1.74, DP1.75, DP1.76, DP1.77, DP1.78, DP1.79, DP1.80, DP1.81, DP1.82, DP1.83, DP1.84, DP1.85, DP1.86, DP1.87, DP1.88, DP1.89, DP1.90, DP1.91, DP1.92, DP1.93, DP1.94, DP1.95, DP1.96, DP1.97, DP1.98, DP1.99, DP1.100, DP1.101, DP1.102, DP1.103, DP1.104, DP1.105, DP1.106, DP1.107, DP1.108, DP1.109, DP1.110, DP1.111, DP1.112, DP1.113, DP1.114, DP1.115, DP1.116, DP1.117, DP1.118, DP1.119, DP1.120, DP1.121, DP1.122, DP1.123, DP1.124, DP1.125, DP1.126, DP1.127, DP1.128, DP1.129, DP1.130, DP1.131, DP1.132, DP1.133, DP1.134, DP1.135, DP1.136, DP1.137, DP1.138, DP1.139, DP1.140, DP1.141, DP1.142, DP1.143, DP1.144, DP1.145, DP1.146, DP1.147, DP1.148, DP1.149, DP1.150, DSP1.1
GPIO_EXT_0: DJ1.31, DP1.31
GPIO_EXT_1: DJ1.32, DP1.32
GPIO_EXT_2: DJ1.33, DP1.33
GPIO_EXT_3: DJ1.34, DP1.34
H3LIS_INT1: DJ1.35, DP1.35
I2C3_SCL: DJ1.36, DP1.36
I2C3_SDA: DJ1.37, DP1.37
JUMP_WAKE: DJ1.38, DP1.38
NRST: DJ1.39, DP1.39
SWO: DJ1.40, DP1.40
SYS_I2C_SCL: DJ1.41, DP1.41
SYS_I2C_SDA: DJ1.42, DP1.42
SYS_SPI_CS_FIN: DJ1.43, DP1.43
SYS_SPI_MISO: DJ1.44, DP1.44
SYS_SPI_MOSI: DJ1.45, DP1.45
SYS_SPI_SCLK: DJ1.46, DP1.46

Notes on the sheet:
D_spacer

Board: 2 copper layers, 5 parts (1 on the bottom side), 46 nets, no tracks yet.

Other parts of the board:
DMH1, DMH2: smash_mech_potting
